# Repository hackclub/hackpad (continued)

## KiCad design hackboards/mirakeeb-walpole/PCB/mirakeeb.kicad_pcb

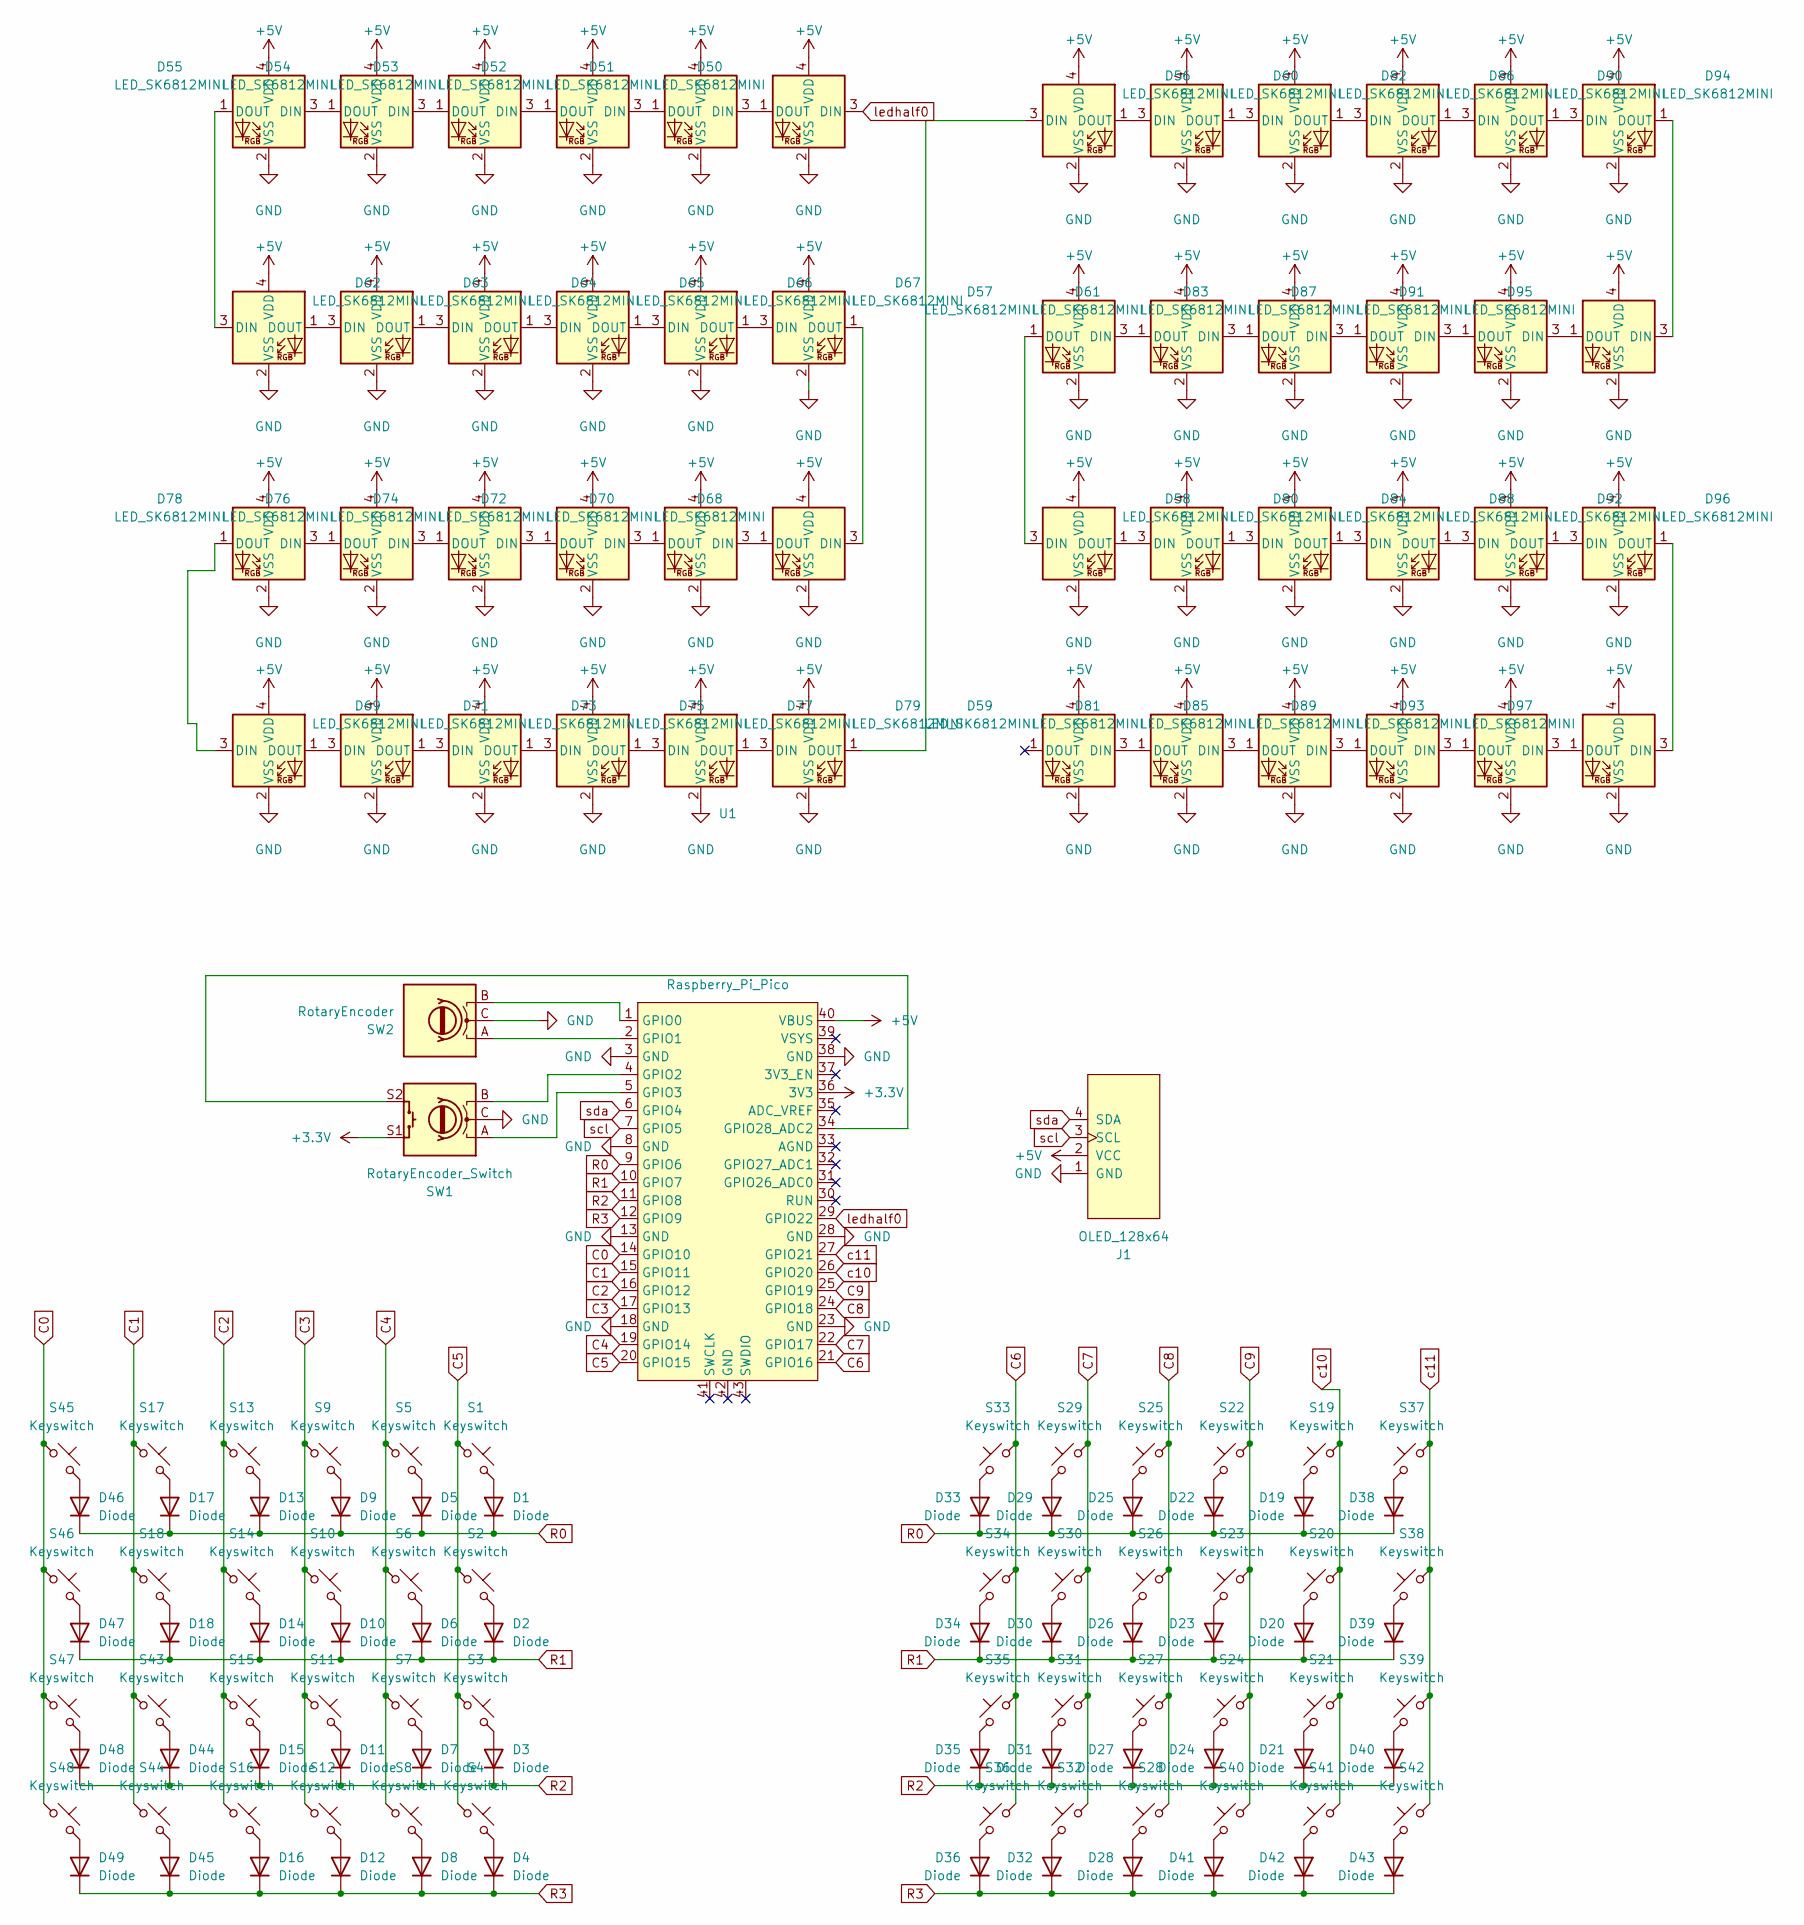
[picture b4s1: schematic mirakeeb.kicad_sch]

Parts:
D1, D2, D3, D4, D5, D6, D7, D8, D9, D10, D11, D12, D13, D14, D15, D16, D17, D18, D19, D20, D21, D22, D23, D24, D25, D26, D27, D28, D29, D30, D31, D32, D33, D34, D35, D36, D38, D39, D40, D41, D42, D43, D44, D45, D46, D47, D48, D49: Diode; Diode_DO-35
D50, D51, D52, D53, D54, D55, D56, D57, D58, D59, D60, D61, D62, D63, D64, D65, D66, D67, D68, D69, D70, D71, D72, D73, D74, D75, D76, D77, D78, D79, D80, D81, D82, D83, D84, D85, D86, D87, D88, D89, D90, D91, D92, D93, D94, D95, D96, D97: LED_SK6812MINI
J1: OLED_128x64
S1, S2, S3, S4, S5, S6, S7, S8, S9, S10, S11, S12, S13, S14, S15, S16, S17, S18, S19, S20, S21, S22, S23, S24, S25, S26, S27, S28, S29, S30, S31, S32, S33, S34, S35, S36, S37, S38, S39, S40, S41, S42, S43, S44, S45, S46, S47, S48: Keyswitch; MX_PCB_1.00u
SW1: RotaryEncoder_Switch; RotaryEncoder_Alps_EC11E-Switch_Vertical_H20mm
SW2: RotaryEncoder; RotaryEncoder_Bourns_Horizontal_PEC09-2xxxF-Nxxxx
U1: Raspberry_Pi_Pico

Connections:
+3.3V: SW1.S1, U1.36 (3V3)
+5V: D50.4 (VDD), D51.4 (VDD), D52.4 (VDD), D53.4 (VDD), D54.4 (VDD), D55.4 (VDD), D56.4 (VDD), D57.4 (VDD), D58.4 (VDD), D59.4 (VDD), D60.4 (VDD), D61.4 (VDD), D62.4 (VDD), D63.4 (VDD), D64.4 (VDD), D65.4 (VDD), D66.4 (VDD), D67.4 (VDD), D68.4 (VDD), D69.4 (VDD), D70.4 (VDD), D71.4 (VDD), D72.4 (VDD), D73.4 (VDD), D74.4 (VDD), D75.4 (VDD), D76.4 (VDD), D77.4 (VDD), D78.4 (VDD), D79.4 (VDD), D80.4 (VDD), D81.4 (VDD), D82.4 (VDD), D83.4 (VDD), D84.4 (VDD), D85.4 (VDD), D86.4 (VDD), D87.4 (VDD), D88.4 (VDD), D89.4 (VDD), D90.4 (VDD), D91.4 (VDD), D92.4 (VDD), D93.4 (VDD), D94.4 (VDD), D95.4 (VDD), D96.4 (VDD), D97.4 (VDD), J1.2 (VCC), U1.40 (VBUS)
C0: S45.1, S46.1, S47.1, S48.1, U1.14 (GPIO10)
C1: S17.1, S18.1, S43.1, S44.1, U1.15 (GPIO11)
C2: S13.1, S14.1, S15.1, S16.1, U1.16 (GPIO12)
C3: S9.1, S10.1, S11.1, S12.1, U1.17 (GPIO13)
C4: S5.1, S6.1, S7.1, S8.1, U1.19 (GPIO14)
C5: S1.1, S2.1, S3.1, S4.1, U1.20 (GPIO15)
C6: S33.1, S34.1, S35.1, S36.1, U1.21 (GPIO16)
C7: S29.1, S30.1, S31.1, S32.1, U1.22 (GPIO17)
C8: S25.1, S26.1, S27.1, S28.1, U1.24 (GPIO18)
C9: S22.1, S23.1, S24.1, S40.1, U1.25 (GPIO19)
GND: D50.2 (VSS), D51.2 (VSS), D52.2 (VSS), D53.2 (VSS), D54.2 (VSS), D55.2 (VSS), D56.2 (VSS), D57.2 (VSS), D58.2 (VSS), D59.2 (VSS), D60.2 (VSS), D61.2 (VSS), D62.2 (VSS), D63.2 (VSS), D64.2 (VSS), D65.2 (VSS), D66.2 (VSS), D67.2 (VSS), D68.2 (VSS), D69.2 (VSS), D70.2 (VSS), D71.2 (VSS), D72.2 (VSS), D73.2 (VSS), D74.2 (VSS), D75.2 (VSS), D76.2 (VSS), D77.2 (VSS), D78.2 (VSS), D79.2 (VSS), D80.2 (VSS), D81.2 (VSS), D82.2 (VSS), D83.2 (VSS), D84.2 (VSS), D85.2 (VSS), D86.2 (VSS), D87.2 (VSS), D88.2 (VSS), D89.2 (VSS), D90.2 (VSS), D91.2 (VSS), D92.2 (VSS), D93.2 (VSS), D94.2 (VSS), D95.2 (VSS), D96.2 (VSS), D97.2 (VSS), J1.1 (GND), SW1.C, SW2.C, U1.3 (GND), U1.8 (GND), U1.13 (GND), U1.18 (GND), U1.23 (GND), U1.28 (GND), U1.38 (GND)
unnamed: D1.2 (A), S1.2
unnamed: D2.2 (A), S2.2
unnamed: D3.2 (A), S3.2
unnamed: D4.2 (A), S4.2
unnamed: D5.2 (A), S5.2
unnamed: D6.2 (A), S6.2
unnamed: D7.2 (A), S7.2
unnamed: D8.2 (A), S8.2
unnamed: D9.2 (A), S9.2
unnamed: D10.2 (A), S10.2
unnamed: D11.2 (A), S11.2
unnamed: D12.2 (A), S12.2
unnamed: D13.2 (A), S13.2
unnamed: D14.2 (A), S14.2
unnamed: D15.2 (A), S15.2
unnamed: D16.2 (A), S16.2
unnamed: D17.2 (A), S17.2
unnamed: D18.2 (A), S18.2
unnamed: D19.2 (A), S19.2
unnamed: D20.2 (A), S20.2
unnamed: D21.2 (A), S21.2
unnamed: D22.2 (A), S22.2
unnamed: D23.2 (A), S23.2
unnamed: D24.2 (A), S24.2
unnamed: D25.2 (A), S25.2
unnamed: D26.2 (A), S26.2
unnamed: D27.2 (A), S27.2
unnamed: D28.2 (A), S28.2
unnamed: D29.2 (A), S29.2
unnamed: D30.2 (A), S30.2
unnamed: D31.2 (A), S31.2
unnamed: D32.2 (A), S32.2
unnamed: D33.2 (A), S33.2
unnamed: D34.2 (A), S34.2
unnamed: D35.2 (A), S35.2
unnamed: D36.2 (A), S36.2
unnamed: D38.2 (A), S37.2
unnamed: D39.2 (A), S38.2
unnamed: D40.2 (A), S39.2
unnamed: D41.2 (A), S40.2
unnamed: D42.2 (A), S41.2
unnamed: D43.2 (A), S42.2
unnamed: D44.2 (A), S43.2
unnamed: D45.2 (A), S44.2
unnamed: D46.2 (A), S45.2
unnamed: D47.2 (A), S46.2
unnamed: D48.2 (A), S47.2
unnamed: D49.2 (A), S48.2
unnamed: D50.1 (DOUT), D51.3 (DIN)
unnamed: D51.1 (DOUT), D52.3 (DIN)
unnamed: D52.1 (DOUT), D53.3 (DIN)
unnamed: D53.1 (DOUT), D54.3 (DIN)
unnamed: D54.1 (DOUT), D55.3 (DIN)
unnamed: D55.1 (DOUT), D62.3 (DIN)
unnamed: D56.3 (DIN), D79.1 (DOUT)
unnamed: D56.1 (DOUT), D60.3 (DIN)
unnamed: D57.3 (DIN), D61.1 (DOUT)
unnamed: D57.1 (DOUT), D58.3 (DIN)
unnamed: D58.1 (DOUT), D80.3 (DIN)
unnamed: D59.3 (DIN), D81.1 (DOUT)
unnamed: D60.1 (DOUT), D82.3 (DIN)
unnamed: D61.3 (DIN), D83.1 (DOUT)
unnamed: D62.1 (DOUT), D63.3 (DIN)
unnamed: D63.1 (DOUT), D64.3 (DIN)
unnamed: D64.1 (DOUT), D65.3 (DIN)
unnamed: D65.1 (DOUT), D66.3 (DIN)
unnamed: D66.1 (DOUT), D67.3 (DIN)
unnamed: D67.1 (DOUT), D68.3 (DIN)
unnamed: D68.1 (DOUT), D70.3 (DIN)
unnamed: D69.3 (DIN), D78.1 (DOUT)
unnamed: D69.1 (DOUT), D71.3 (DIN)
unnamed: D70.1 (DOUT), D72.3 (DIN)
unnamed: D71.1 (DOUT), D73.3 (DIN)
unnamed: D72.1 (DOUT), D74.3 (DIN)
unnamed: D73.1 (DOUT), D75.3 (DIN)
unnamed: D74.1 (DOUT), D76.3 (DIN)
unnamed: D75.1 (DOUT), D77.3 (DIN)
unnamed: D76.1 (DOUT), D78.3 (DIN)
unnamed: D77.1 (DOUT), D79.3 (DIN)
unnamed: D80.1 (DOUT), D84.3 (DIN)
unnamed: D81.3 (DIN), D85.1 (DOUT)
unnamed: D82.1 (DOUT), D86.3 (DIN)
unnamed: D83.3 (DIN), D87.1 (DOUT)
unnamed: D84.1 (DOUT), D88.3 (DIN)
unnamed: D85.3 (DIN), D89.1 (DOUT)
unnamed: D86.1 (DOUT), D90.3 (DIN)
unnamed: D87.3 (DIN), D91.1 (DOUT)
unnamed: D88.1 (DOUT), D92.3 (DIN)
unnamed: D89.3 (DIN), D93.1 (DOUT)
unnamed: D90.1 (DOUT), D94.3 (DIN)
unnamed: D91.3 (DIN), D95.1 (DOUT)
unnamed: D92.1 (DOUT), D96.3 (DIN)
unnamed: D93.3 (DIN), D97.1 (DOUT)
unnamed: D94.1 (DOUT), D95.3 (DIN)
unnamed: D96.1 (DOUT), D97.3 (DIN)
unnamed: SW2.B, U1.1 (GPIO0)
unnamed: SW2.A, U1.2 (GPIO1)
unnamed: SW1.B, U1.4 (GPIO2)
unnamed: SW1.A, U1.5 (GPIO3)
unnamed: SW1.S2, U1.34 (GPIO28_ADC2)
R0: D1.1 (K), D5.1 (K), D9.1 (K), D13.1 (K), D17.1 (K), D19.1 (K), D22.1 (K), D25.1 (K), D29.1 (K), D33.1 (K), D38.1 (K), D46.1 (K), U1.9 (GPIO6)
R1: D2.1 (K), D6.1 (K), D10.1 (K), D14.1 (K), D18.1 (K), D20.1 (K), D23.1 (K), D26.1 (K), D30.1 (K), D34.1 (K), D39.1 (K), D47.1 (K), U1.10 (GPIO7)
R2: D3.1 (K), D7.1 (K), D11.1 (K), D15.1 (K), D21.1 (K), D24.1 (K), D27.1 (K), D31.1 (K), D35.1 (K), D40.1 (K), D44.1 (K), D48.1 (K), U1.11 (GPIO8)
R3: D4.1 (K), D8.1 (K), D12.1 (K), D16.1 (K), D28.1 (K), D32.1 (K), D36.1 (K), D41.1 (K), D42.1 (K), D43.1 (K), D45.1 (K), D49.1 (K), U1.12 (GPIO9)
c10: S19.1, S20.1, S21.1, S41.1, U1.26 (GPIO20)
c11: S37.1, S38.1, S39.1, S42.1, U1.27 (GPIO21)
ledhalf0: D50.3 (DIN), U1.29 (GPIO22)
scl: J1.3 (SCL), U1.7 (GPIO5)
sda: J1.4 (SDA), U1.6 (GPIO4)

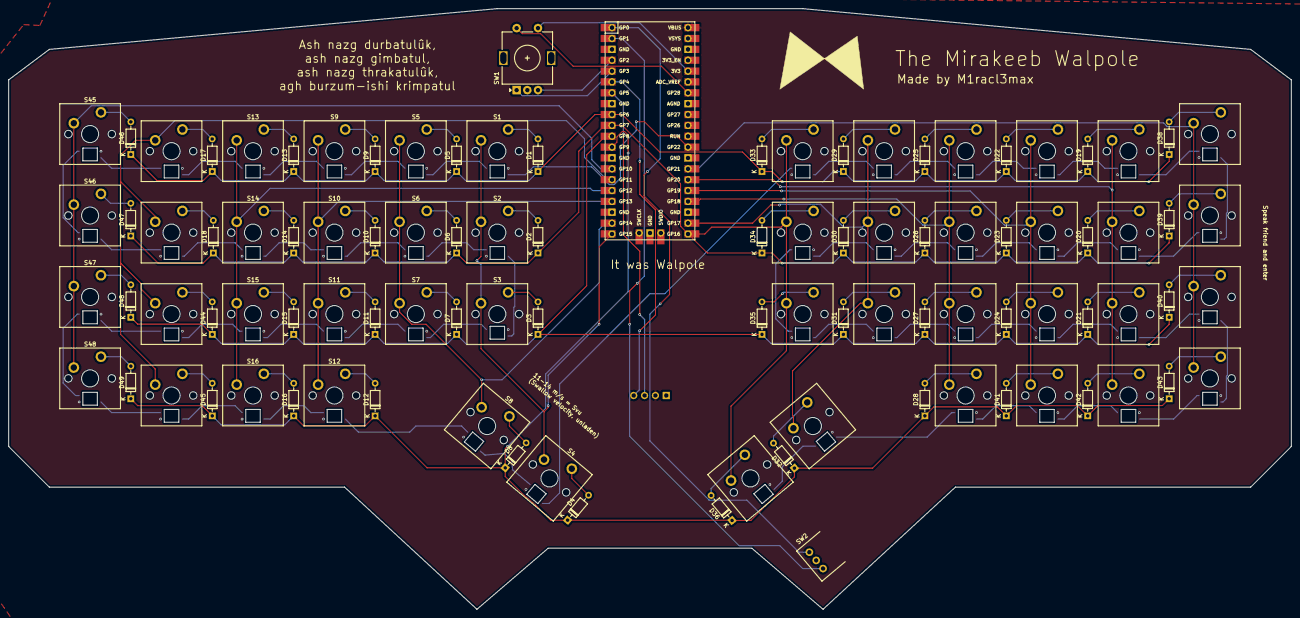
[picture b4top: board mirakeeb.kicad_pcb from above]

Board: 2 copper layers, 300.0 x 140.5 mm, 148 parts (0 on the bottom side), 122 nets.

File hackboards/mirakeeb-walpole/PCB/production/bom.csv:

Designator,Footprint,Quantity,Value,LCSC Part #
"D1, D10, D11, D12, D13, D14, D15, D16, D17, D18, D19, D2, D20, D21, D22, D23, D24, D25, D26, D27, D28, D29, D3, D30, D31, D32, D33, D34, D35, D36, D38, D39, D4, D40, D41, D42, D43, D44, D45, D46, D47, D48, D49, D5, D6, D7, D8, D9",Diode_DO-35,48,Diode,
"D50, D51, D52, D53, D54, D55, D56, D57, D58, D59, D60, D61, D62, D63, D64, D65, D66, D67, D68, D69, D70, D71, D72, D73, D74, D75, D76, D77, D78, D79, D80, D81, D82, D83, D84, D85, D86, D87, D88, D89, D90, D91, D92, D93, D94, D95, D96, D97",LED_SK6812MINI,48,LED_SK6812MINI,
J1,OLED_128x64,1,OLED_128x64,
"S1, S10, S11, S12, S13, S14, S15, S16, S17, S18, S19, S2, S20, S21, S22, S23, S24, S25, S26, S27, S28, S29, S3, S30, S31, S32, S33, S34, S35, S36, S37, S38, S39, S4, S40, S41, S42, S43, S44, S45, S46, S47, S48, S5, S6, S7, S8, S9",MX_PCB_1.00u,48,Keyswitch,
SW1,RotaryEncoder_Alps_EC11E-Switch_Vertical_H20mm,1,RotaryEncoder_Switch,
SW2,RotaryEncoder_Bourns_Horizontal_PEC09-2xxxF-Nxxxx,1,RotaryEncoder,
U1,Raspberry_Pi_Pico,1,Raspberry_Pi_Pico,

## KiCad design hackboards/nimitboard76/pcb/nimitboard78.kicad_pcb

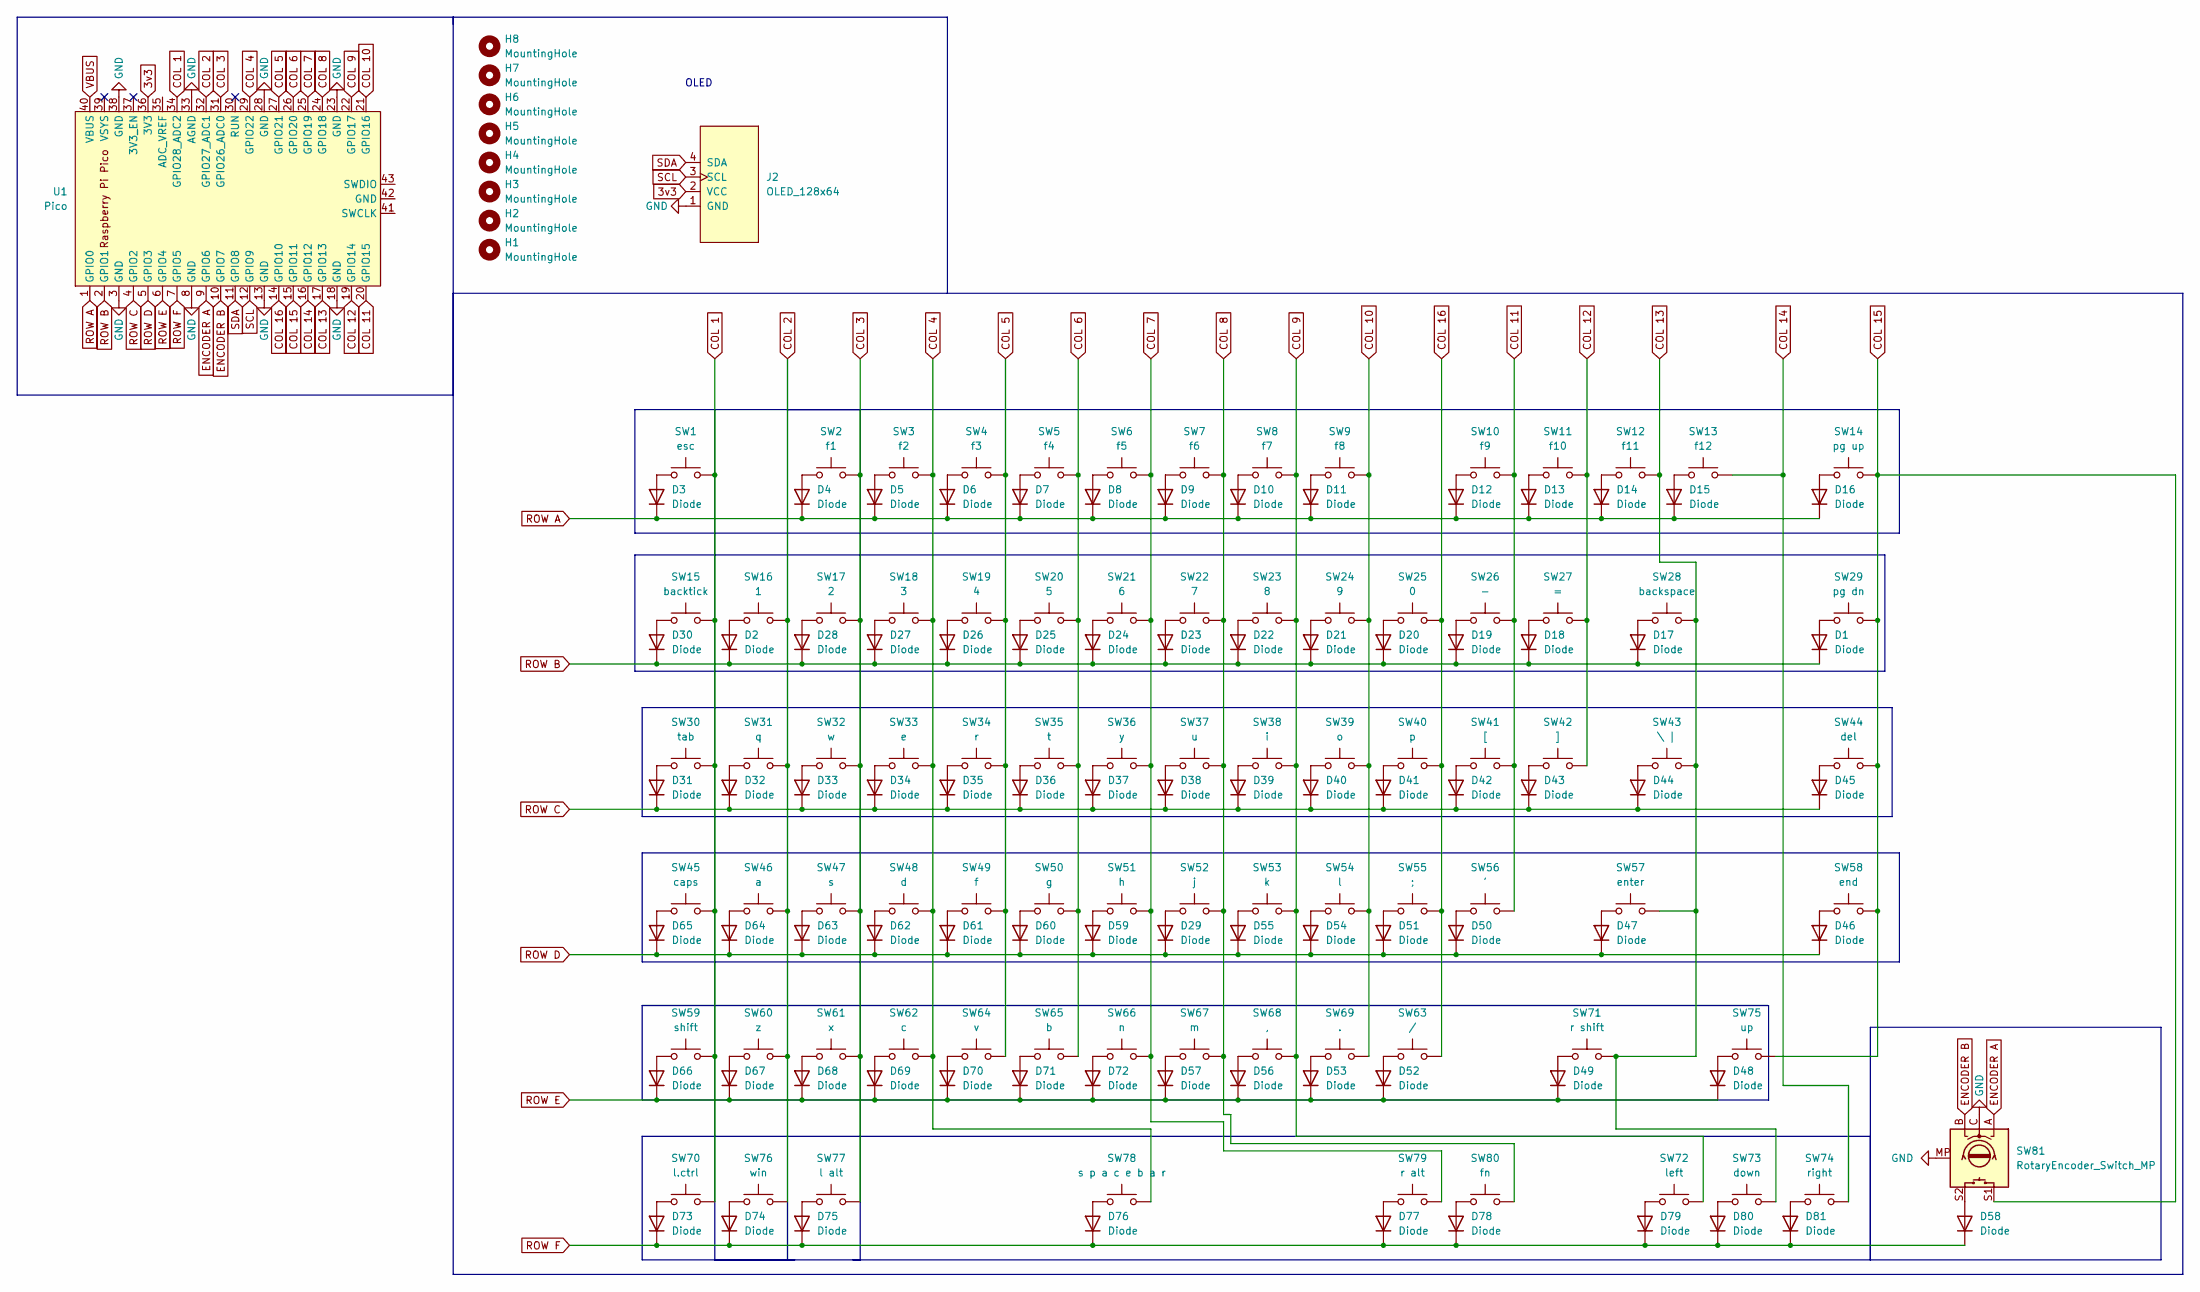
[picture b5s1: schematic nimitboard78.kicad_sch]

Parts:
D1, D2, D3, D4, D5, D6, D7, D8, D9, D10, D11, D12, D13, D14, D15, D16, D17, D18, D19, D20, D21, D22, D23, D24, D25, D26, D27, D28, D29, D30, D31, D32, D33, D34, D35, D36, D37, D38, D39, D40, D41, D42, D43, D44, D45, D46, D47, D48, D49, D50, D51, D52, D53, D54, D55, D56, D57, D58, D59, D60, D61, D62, D63, D64, D65, D66, D67, D68, D69, D70, D71, D72, D73, D74, D75, D76, D77, D78, D79, D80, D81: Diode; D_DO-35_SOD27_P7.62mm_Horizontal
H1, H2, H3, H4, H5, H6, H7, H8: MountingHole; MountingHole_3.2mm_M3
J2: OLED_128x64; PinHeader_1x04_P2.54mm_Vertical
SW1: esc; SW_Cherry_MX_1.00u_PCB
SW2: f1; SW_Cherry_MX_1.00u_PCB
SW3: f2; SW_Cherry_MX_1.00u_PCB
SW4: f3; SW_Cherry_MX_1.00u_PCB
SW5: f4; SW_Cherry_MX_1.00u_PCB
SW6: f5; SW_Cherry_MX_1.00u_PCB
SW7: f6; SW_Cherry_MX_1.00u_PCB
SW8: f7; SW_Cherry_MX_1.00u_PCB
SW9: f8; SW_Cherry_MX_1.00u_PCB
SW10: f9; SW_Cherry_MX_1.00u_PCB
SW11: f10; SW_Cherry_MX_1.00u_PCB
SW12: f11; SW_Cherry_MX_1.00u_PCB
SW13: f12; SW_Cherry_MX_1.00u_PCB
SW14: pg up; SW_Cherry_MX_1.00u_PCB
SW15: backtick; SW_Cherry_MX_1.00u_PCB
SW16: 1; SW_Cherry_MX_1.00u_PCB
SW17: 2; SW_Cherry_MX_1.00u_PCB
SW18: 3; SW_Cherry_MX_1.00u_PCB
SW19: 4; SW_Cherry_MX_1.00u_PCB
SW20: 5; SW_Cherry_MX_1.00u_PCB
SW21: 6; SW_Cherry_MX_1.00u_PCB
SW22: 7; SW_Cherry_MX_1.00u_PCB
SW23: 8; SW_Cherry_MX_1.00u_PCB
SW24: 9; SW_Cherry_MX_1.00u_PCB
SW25: 0; SW_Cherry_MX_1.00u_PCB
SW26: -; SW_Cherry_MX_1.00u_PCB
SW27: =; SW_Cherry_MX_1.00u_PCB
SW28: backspace; SW_Cherry_MX_2.00u_PCB
SW29: pg dn; SW_Cherry_MX_1.00u_PCB
SW30: tab; SW_Cherry_MX_1.50u_PCB
SW31: q; SW_Cherry_MX_1.00u_PCB
SW32: w; SW_Cherry_MX_1.00u_PCB
SW33: e; SW_Cherry_MX_1.00u_PCB
SW34: r; SW_Cherry_MX_1.00u_PCB
SW35: t; SW_Cherry_MX_1.00u_PCB
SW36: y; SW_Cherry_MX_1.00u_PCB
SW37: u; SW_Cherry_MX_1.00u_PCB
SW38: i; SW_Cherry_MX_1.00u_PCB
SW39: o; SW_Cherry_MX_1.00u_PCB
SW40: p; SW_Cherry_MX_1.00u_PCB
SW41: [; SW_Cherry_MX_1.00u_PCB
SW42: ]; SW_Cherry_MX_1.00u_PCB
SW43: \ |; SW_Cherry_MX_1.50u_PCB
SW44: del; SW_Cherry_MX_1.00u_PCB
SW45: caps; SW_Cherry_MX_1.75u_PCB
SW46: a; SW_Cherry_MX_1.00u_PCB
SW47: s; SW_Cherry_MX_1.00u_PCB
SW48: d; SW_Cherry_MX_1.00u_PCB
SW49: f; SW_Cherry_MX_1.00u_PCB
SW50: g; SW_Cherry_MX_1.00u_PCB
SW51: h; SW_Cherry_MX_1.00u_PCB
SW52: j; SW_Cherry_MX_1.00u_PCB
SW53: k; SW_Cherry_MX_1.00u_PCB
SW54: l; SW_Cherry_MX_1.00u_PCB
SW55: ;; SW_Cherry_MX_1.00u_PCB
SW56: '; SW_Cherry_MX_1.00u_PCB
SW57: enter; SW_Cherry_MX_2.25u_PCB
SW58: end; SW_Cherry_MX_1.00u_PCB
SW59: shift; SW_Cherry_MX_2.25u_PCB
SW60: z; SW_Cherry_MX_1.00u_PCB
SW61: x; SW_Cherry_MX_1.00u_PCB
SW62: c; SW_Cherry_MX_1.00u_PCB
SW63: /; SW_Cherry_MX_1.00u_PCB
SW64: v; SW_Cherry_MX_1.00u_PCB
SW65: b; SW_Cherry_MX_1.00u_PCB
SW66: n; SW_Cherry_MX_1.00u_PCB
SW67: m; SW_Cherry_MX_1.00u_PCB
SW68: ,; SW_Cherry_MX_1.00u_PCB
SW69: .; SW_Cherry_MX_1.00u_PCB
SW70: l.ctrl; SW_Cherry_MX_1.25u_PCB
SW71: r shift; SW_Cherry_MX_1.75u_PCB
SW72: left; SW_Cherry_MX_1.00u_PCB
SW73: down; SW_Cherry_MX_1.00u_PCB
SW74: right; SW_Cherry_MX_1.00u_PCB
SW75: up; SW_Cherry_MX_1.00u_PCB
SW76: win; SW_Cherry_MX_1.25u_PCB
SW77: l alt; SW_Cherry_MX_1.25u_PCB
SW78: s p a c e b a r; SW_Cherry_MX_6.25u_PCB
SW79: r alt; SW_Cherry_MX_1.25u_PCB
SW80: fn; SW_Cherry_MX_1.25u_PCB
SW81: RotaryEncoder_Switch_MP; RotaryEncoder_Alps_EC11E-Switch_Vertical_H20mm
U1: Pico; RPi_Pico_SMD_TH

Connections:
3v3: J2.2 (VCC), U1.36 (3V3)
COL 1: SW1.2, SW15.2, SW30.2, SW45.2, SW59.2, SW70.2, U1.34 (GPIO28_ADC2)
COL 2: SW16.2, SW31.2, SW46.2, SW60.2, SW76.2, U1.32 (GPIO27_ADC1)
COL 3: SW2.2, SW17.2, SW32.2, SW47.2, SW61.2, SW77.2, U1.31 (GPIO26_ADC0)
COL 4: SW3.2, SW18.2, SW33.2, SW48.2, SW62.2, SW78.2, U1.29 (GPIO22)
COL 5: SW4.2, SW19.2, SW34.2, SW49.2, SW64.2, U1.27 (GPIO21)
COL 6: SW5.2, SW20.2, SW35.2, SW50.2, SW65.2, U1.26 (GPIO20)
COL 7: SW6.2, SW21.2, SW36.2, SW51.2, SW66.2, SW79.2, U1.25 (GPIO19)
COL 8: SW7.2, SW22.2, SW37.2, SW52.2, SW67.2, SW80.2, U1.24 (GPIO18)
COL 9: SW8.2, SW23.2, SW38.2, SW53.2, SW68.2, SW72.2, U1.22 (GPIO17)
COL 10: SW9.2, SW24.2, SW39.2, SW54.2, SW69.2, U1.21 (GPIO16)
COL 11: SW10.2, SW26.2, SW41.2, SW56.2, U1.20 (GPIO15)
COL 12: SW11.2, SW27.2, SW42.2, U1.19 (GPIO14)
COL 13: SW12.2, SW28.2, SW43.2, SW57.2, SW71.2, SW73.2, U1.17 (GPIO13)
COL 14: SW13.2, SW74.2, U1.16 (GPIO12)
COL 15: SW14.2, SW29.2, SW44.2, SW58.2, SW75.2, SW81.S1, U1.15 (GPIO11)
COL 16: SW25.2, SW40.2, SW55.2, SW63.2, U1.14 (GPIO10)
ENCODER A: SW81.A, U1.9 (GPIO6)
ENCODER B: SW81.B, U1.10 (GPIO7)
GND: J2.1 (GND), SW81.C, SW81.MP, U1.3 (GND), U1.8 (GND), U1.13 (GND), U1.18 (GND), U1.23 (GND), U1.28 (GND), U1.33 (AGND), U1.38 (GND)
unnamed: D1.2 (A), SW29.1
unnamed: D2.2 (A), SW16.1
unnamed: D3.2 (A), SW1.1
unnamed: D4.2 (A), SW2.1
unnamed: D5.2 (A), SW3.1
unnamed: D6.2 (A), SW4.1
unnamed: D7.2 (A), SW5.1
unnamed: D8.2 (A), SW6.1
unnamed: D9.2 (A), SW7.1
unnamed: D10.2 (A), SW8.1
unnamed: D11.2 (A), SW9.1
unnamed: D12.2 (A), SW10.1
unnamed: D13.2 (A), SW11.1
unnamed: D14.2 (A), SW12.1
unnamed: D15.2 (A), SW13.1
unnamed: D16.2 (A), SW14.1
unnamed: D17.2 (A), SW28.1
unnamed: D18.2 (A), SW27.1
unnamed: D19.2 (A), SW26.1
unnamed: D20.2 (A), SW25.1
unnamed: D21.2 (A), SW24.1
unnamed: D22.2 (A), SW23.1
unnamed: D23.2 (A), SW22.1
unnamed: D24.2 (A), SW21.1
unnamed: D25.2 (A), SW20.1
unnamed: D26.2 (A), SW19.1
unnamed: D27.2 (A), SW18.1
unnamed: D28.2 (A), SW17.1
unnamed: D29.2 (A), SW52.1
unnamed: D30.2 (A), SW15.1
unnamed: D31.2 (A), SW30.1
unnamed: D32.2 (A), SW31.1
unnamed: D33.2 (A), SW32.1
unnamed: D34.2 (A), SW33.1
unnamed: D35.2 (A), SW34.1
unnamed: D36.2 (A), SW35.1
unnamed: D37.2 (A), SW36.1
unnamed: D38.2 (A), SW37.1
unnamed: D39.2 (A), SW38.1
unnamed: D40.2 (A), SW39.1
unnamed: D41.2 (A), SW40.1
unnamed: D42.2 (A), SW41.1
unnamed: D43.2 (A), SW42.1
unnamed: D44.2 (A), SW43.1
unnamed: D45.2 (A), SW44.1
unnamed: D46.2 (A), SW58.1
unnamed: D47.2 (A), SW57.1
unnamed: D48.2 (A), SW75.1
unnamed: D49.2 (A), SW71.1
unnamed: D50.2 (A), SW56.1
unnamed: D51.2 (A), SW55.1
unnamed: D52.2 (A), SW63.1
unnamed: D53.2 (A), SW69.1
unnamed: D54.2 (A), SW54.1
unnamed: D55.2 (A), SW53.1
unnamed: D56.2 (A), SW68.1
unnamed: D57.2 (A), SW67.1
unnamed: D58.2 (A), SW81.S2
unnamed: D59.2 (A), SW51.1
unnamed: D60.2 (A), SW50.1
unnamed: D61.2 (A), SW49.1
unnamed: D62.2 (A), SW48.1
unnamed: D63.2 (A), SW47.1
unnamed: D64.2 (A), SW46.1
unnamed: D65.2 (A), SW45.1
unnamed: D66.2 (A), SW59.1
unnamed: D67.2 (A), SW60.1
unnamed: D68.2 (A), SW61.1
unnamed: D69.2 (A), SW62.1
unnamed: D70.2 (A), SW64.1
unnamed: D71.2 (A), SW65.1
unnamed: D72.2 (A), SW66.1
unnamed: D73.2 (A), SW70.1
unnamed: D74.2 (A), SW76.1
unnamed: D75.2 (A), SW77.1
unnamed: D76.2 (A), SW78.1
unnamed: D77.2 (A), SW79.1
unnamed: D78.2 (A), SW80.1
unnamed: D79.2 (A), SW72.1
unnamed: D80.2 (A), SW73.1
unnamed: D81.2 (A), SW74.1
ROW A: D3.1 (K), D4.1 (K), D5.1 (K), D6.1 (K), D7.1 (K), D8.1 (K), D9.1 (K), D10.1 (K), D11.1 (K), D12.1 (K), D13.1 (K), D14.1 (K), D15.1 (K), D16.1 (K), U1.1 (GPIO0)
ROW B: D1.1 (K), D2.1 (K), D17.1 (K), D18.1 (K), D19.1 (K), D20.1 (K), D21.1 (K), D22.1 (K), D23.1 (K), D24.1 (K), D25.1 (K), D26.1 (K), D27.1 (K), D28.1 (K), D30.1 (K), U1.2 (GPIO1)
ROW C: D31.1 (K), D32.1 (K), D33.1 (K), D34.1 (K), D35.1 (K), D36.1 (K), D37.1 (K), D38.1 (K), D39.1 (K), D40.1 (K), D41.1 (K), D42.1 (K), D43.1 (K), D44.1 (K), D45.1 (K), U1.4 (GPIO2)
ROW D: D29.1 (K), D46.1 (K), D47.1 (K), D50.1 (K), D51.1 (K), D54.1 (K), D55.1 (K), D59.1 (K), D60.1 (K), D61.1 (K), D62.1 (K), D63.1 (K), D64.1 (K), D65.1 (K), U1.5 (GPIO3)
ROW E: D48.1 (K), D49.1 (K), D52.1 (K), D53.1 (K), D56.1 (K), D57.1 (K), D66.1 (K), D67.1 (K), D68.1 (K), D69.1 (K), D70.1 (K), D71.1 (K), D72.1 (K), U1.6 (GPIO4)
ROW F: D58.1 (K), D73.1 (K), D74.1 (K), D75.1 (K), D76.1 (K), D77.1 (K), D78.1 (K), D79.1 (K), D80.1 (K), D81.1 (K), U1.7 (GPIO5)
SCL: J2.3 (SCL), U1.12 (GPIO9)
SDA: J2.4 (SDA), U1.11 (GPIO8)
VBUS: U1.40 (VBUS)

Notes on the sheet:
OLED

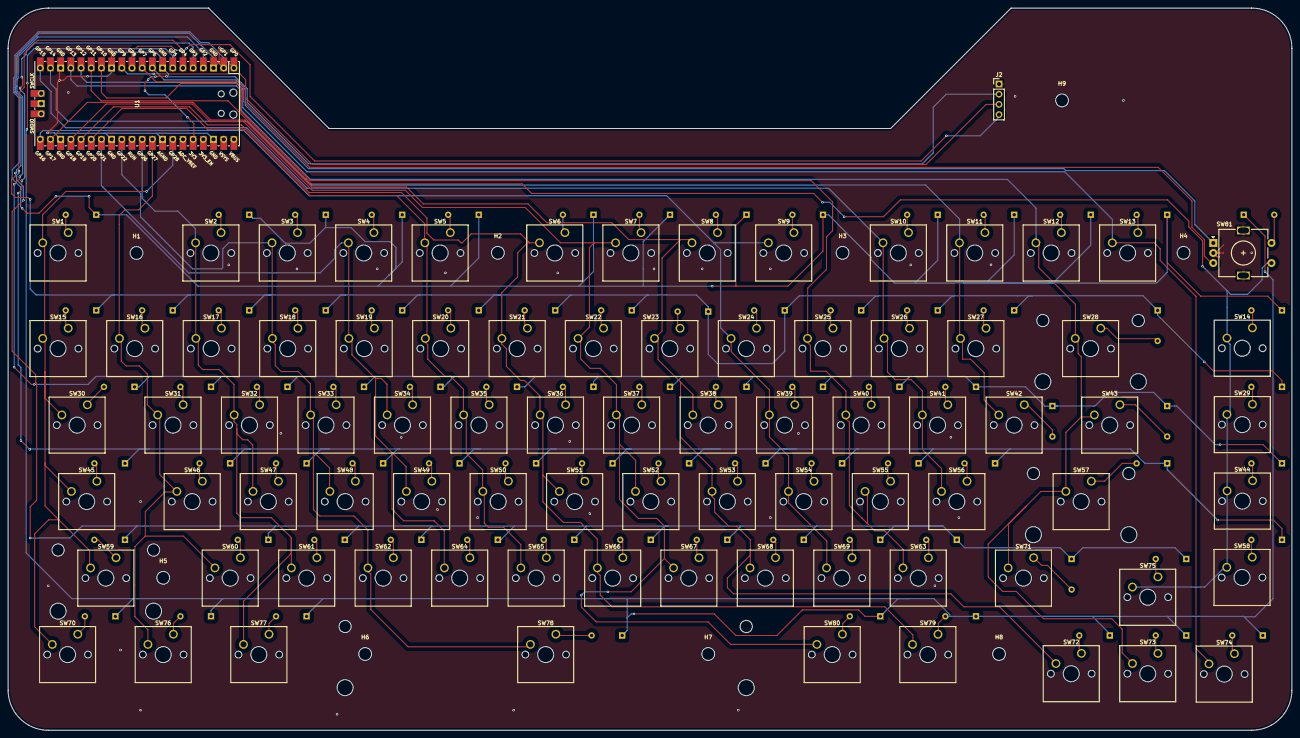
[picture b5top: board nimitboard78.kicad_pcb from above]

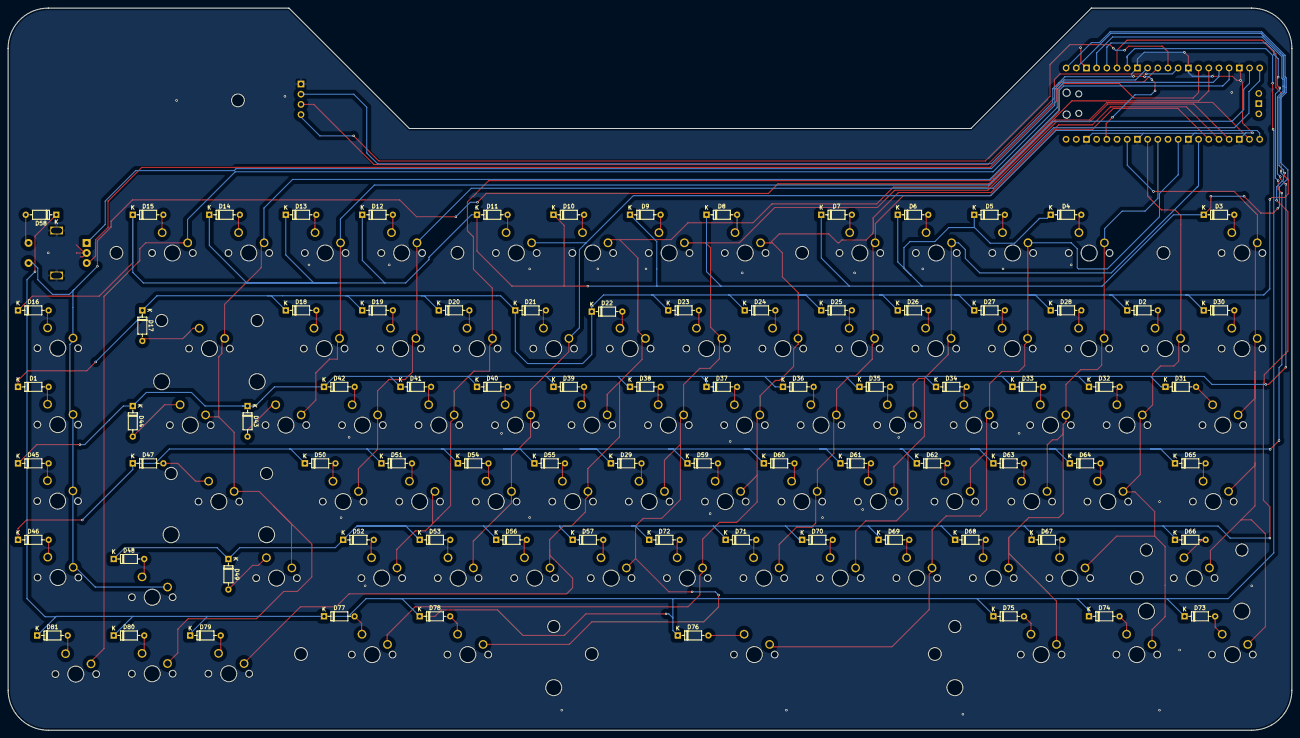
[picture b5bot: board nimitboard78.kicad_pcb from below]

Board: 2 copper layers, 320.0 x 180.0 mm, 173 parts (81 on the bottom side), 109 nets.

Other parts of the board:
H9: MountingHole; MountingHole_3.2mm_M3
